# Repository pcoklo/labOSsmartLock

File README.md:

# labOSsmartLock
its a secret project, muahahahahaaa!

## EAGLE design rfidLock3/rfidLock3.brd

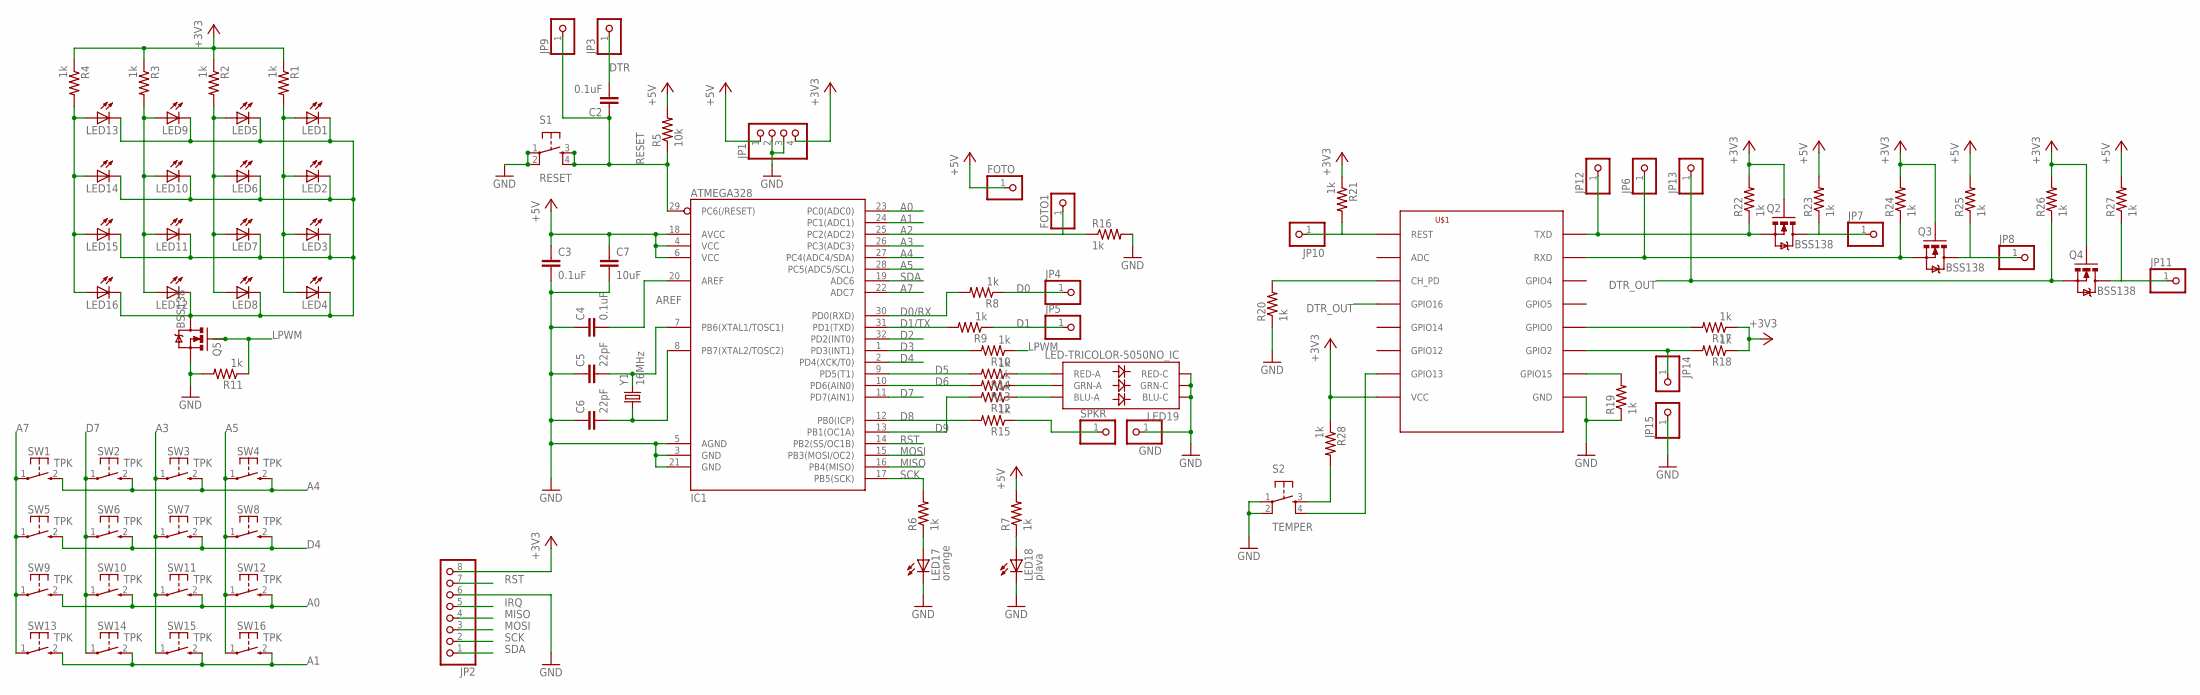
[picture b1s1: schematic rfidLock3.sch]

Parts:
C2, C3, C4: 0.1uF; 0805
C5, C6: 22pF; 0805
C7: 10uF; C3216
FOTO, FOTO1: PINHD-1X1; 1X01
GND: PINHD-1X1; 1X01
IC1: ATMEGA328; TQFP32-08
JP1: PINHD-1X4; 1X04
JP2: PINHD-1X8; 1X08
JP3, JP4, JP5, JP6, JP7, JP8, JP9, JP10, JP11, JP12, JP13, JP14, JP15: PINHD-1X1; 1X01
LED1, LED2, LED3, LED4, LED5, LED6, LED7, LED8, LED9, LED10, LED11, LED12, LED13, LED14, LED15, LED16: LED_E; LED_1206
LED17: orange; CHIP-LED0805
LED18: plava; CHIP-LED0805
LED19: LED-TRICOLOR-5050NO_IC; LED-TRICOLOR-5050
Q2, Q3, Q4, Q5: BSS138; SOT23-3
R1, R2, R3, R4, R6, R7, R8, R9, R10, R11, R12, R13, R14, R15, R16, R17, R18, R19, R20, R21, R22, R23, R24, R25, R26, R27, R28: 1k; 0805
R5: 10k; 0805
S1: RESET; TACTILE_SWITCH_SMD
S2: TEMPER; TACTILE_SWITCH_SMD
SPKR: PINHD-1X1; 1X01
SW1, SW2, SW3, SW4, SW5, SW6, SW7, SW8, SW9, SW10, SW11, SW12, SW13, SW14, SW15, SW16: TPK; KSS-2EG4430
U$1: ESP8266-07; ESP-07
Y1: 16MHz; CRYSTAL-SMD-5X3

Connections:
+3V3: JP1.4, JP2.8, Q2.1 (G), Q3.1 (G), Q4.1 (G), R1.1, R2.1, R3.1, R4.1, R17.1, R18.1, R21.1, R22.2, R24.2, R26.2, R28.1, U$1.VCC
+5V: C3.1, C7.1, FOTO.1, IC1.4 (VCC), IC1.6 (VCC), IC1.18 (AVCC), JP1.1, R5.2, R7.2, R23.2, R25.2, R27.2
A0: IC1.23 (PC0(ADC0)), SW9.2 (S), SW10.2 (S), SW11.2 (S), SW12.2 (S)
A1: IC1.24 (PC1(ADC1)), SW13.2 (S), SW14.2 (S), SW15.2 (S), SW16.2 (S)
A2: FOTO1.1, IC1.25 (PC2(ADC2)), R16.1
A3: IC1.26 (PC3(ADC3)), SW3.1, SW7.1, SW11.1, SW15.1
A4: IC1.27 (PC4(ADC4/SDA)), SW1.2 (S), SW2.2 (S), SW3.2 (S), SW4.2 (S)
A5: IC1.28 (PC5(ADC5/SCL)), SW4.1, SW8.1, SW12.1, SW16.1
A7: IC1.22 (ADC7), SW1.1, SW5.1, SW9.1, SW13.1
AREF: C4.2, IC1.20 (AREF)
CRYSTAL1: C5.2, IC1.7 (PB6(XTAL1/TOSC1)), Y1.3 (2)
CRYSTAL2: C6.2, IC1.8 (PB7(XTAL2/TOSC2)), Y1.1
D0: JP4.1, R8.1
D0/RX: IC1.30 (PD0(RXD)), R8.2
D1: JP5.1, R9.1
D1/TX: IC1.31 (PD1(TXD)), R9.2
D2: IC1.32 (PD2(INT0))
D3: IC1.1 (PD3(INT1)), R10.2
D4: IC1.2 (PD4(XCK/T0)), SW5.2 (S), SW6.2 (S), SW7.2 (S), SW8.2 (S)
D5: IC1.9 (PD5(T1)), R14.2
D6: IC1.10 (PD6(AIN0)), R13.2
D7: IC1.11 (PD7(AIN1)), SW2.1, SW6.1, SW10.1, SW14.1
D8: IC1.12 (PB0(ICP)), R15.2
D9: IC1.13 (PB1(OC1A)), R12.2
DTR: C2.2, JP3.1
DTR_OUT: JP13.1, Q4.2 (S), R26.1, U$1.GPIO16
GND: C3.2, C4.1, C5.1, C6.1, C7.2, GND.1, IC1.3 (GND), IC1.5 (AGND), IC1.21 (GND), JP1.2, JP1.3, JP2.6, JP15.1, LED17.C, LED18.C, LED19.4 (BLU-C), LED19.5 (RED-C), LED19.6 (GRN-C), Q5.2 (S), R11.2, R16.2, R19.1, R20.1, S1.1, S1.2, S2.1, S2.2, U$1.GND
HV1: JP7.1, Q2.3 (D), R23.1
HV2: JP8.1, Q3.3 (D), R25.1
HV3: JP11.1, Q4.3 (D), R27.1
IRQ: JP2.5
LGND: LED1.C, LED2.C, LED3.C, LED4.C, LED5.C, LED6.C, LED7.C, LED8.C, LED9.C, LED10.C, LED11.C, LED12.C, LED13.C, LED14.C, LED15.C, LED16.C, Q5.3 (D)
LPWM: Q5.1 (G), R10.1, R11.1
LV1: JP12.1, Q2.2 (S), R22.1, U$1.TXD
LV2: JP6.1, Q3.2 (S), R24.1, U$1.RXD
MISO: IC1.16 (PB4(MISO)), JP2.4
MOSI: IC1.15 (PB3(MOSI/OC2)), JP2.3
unnamed: LED9.A, LED10.A, LED11.A, LED12.A, R3.2
unnamed: LED13.A, LED14.A, LED15.A, LED16.A, R4.2
unnamed: LED5.A, LED6.A, LED7.A, LED8.A, R2.2
unnamed: LED1.A, LED2.A, LED3.A, LED4.A, R1.2
unnamed: LED17.A, R6.1
unnamed: LED19.1 (GRN-A), R13.1
unnamed: LED18.A, R7.1
unnamed: LED19.2 (RED-A), R14.1
unnamed: LED19.3 (BLU-A), R12.1
unnamed: R15.1, SPKR.1
unnamed: R17.2, U$1.GPIO0
unnamed: JP14.1, R18.2, U$1.GPIO2
unnamed: R19.2, U$1.GPIO15
unnamed: R20.2, U$1.CH_PD
unnamed: JP10.1, R21.2, U$1.REST
unnamed: R28.2, S2.3
unnamed: S2.4, U$1.GPIO13
RESET: C2.1, IC1.29 (PC6(/RESET)), JP9.1, R5.1, S1.3, S1.4
RST: IC1.14 (PB2(SS/OC1B)), JP2.7
SCK: IC1.17 (PB5(SCK)), JP2.2, R6.2
SDA: IC1.19 (ADC6), JP2.1

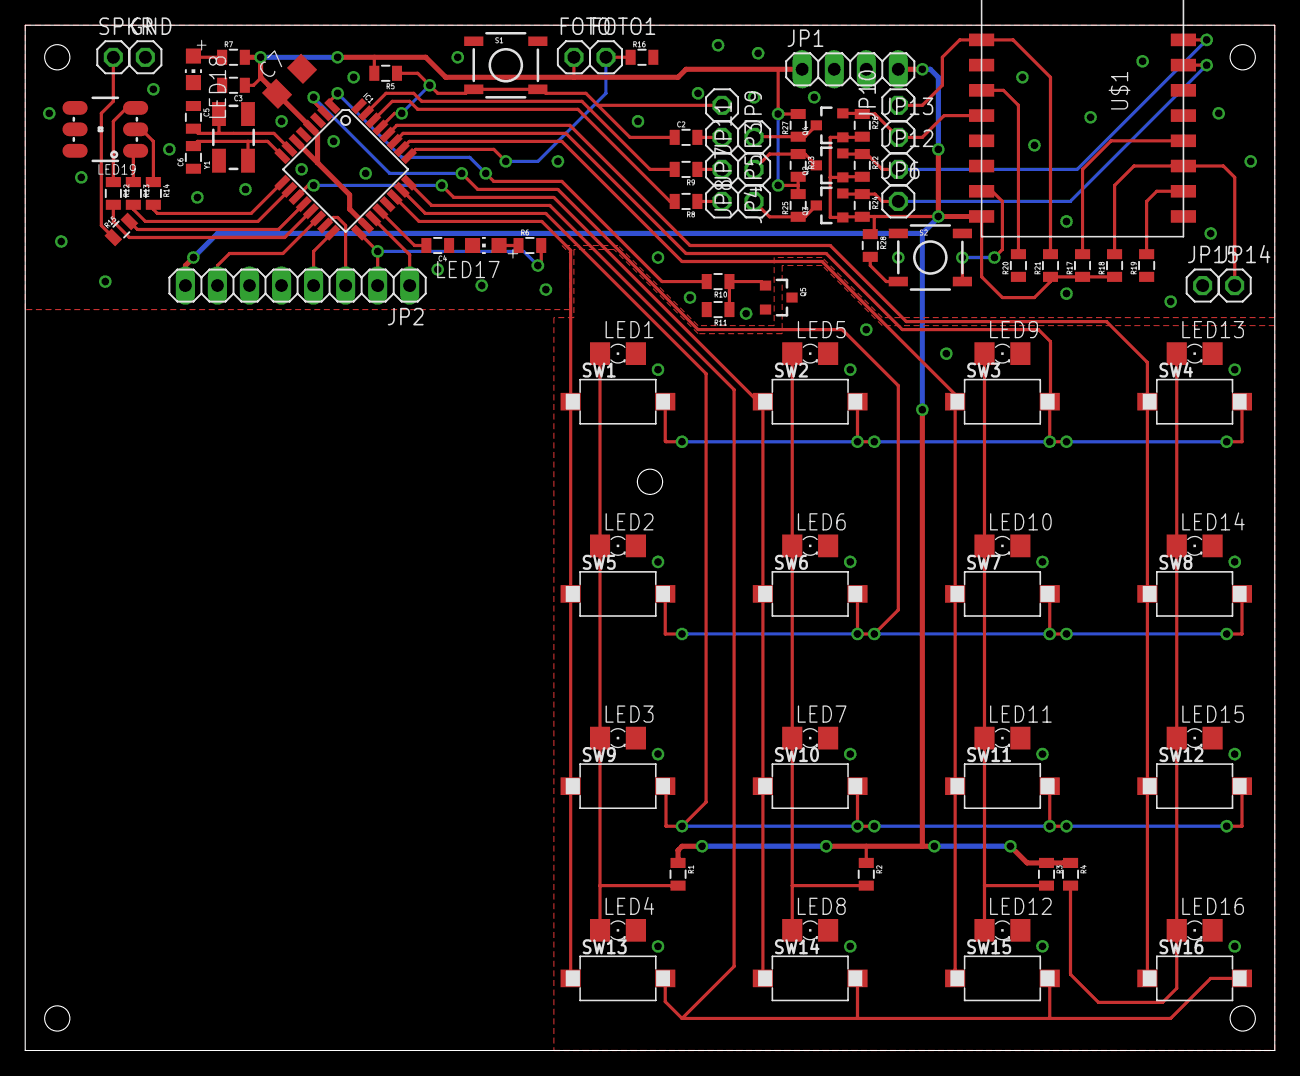
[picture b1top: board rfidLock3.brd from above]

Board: 2 copper layers, 99.1 x 81.3 mm, 97 parts (0 on the bottom side), 56 nets.

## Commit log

2016-01-09 keypad and leds
2016-01-15 pcb update
2016-01-16 another update
2016-01-16 update again
2016-01-18 +led, +conectors...
2016-01-21 almost final version

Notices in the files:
parts and their libraries:
SparkFun: Licensing: CC v3.0 Share-Alike You are welcome to use this library for commercial purposes.
SparkFun-LED: Licensing: Creative Commons ShareAlike 4.0 International - https://creativecommons.org/licenses/by-sa/4.0
